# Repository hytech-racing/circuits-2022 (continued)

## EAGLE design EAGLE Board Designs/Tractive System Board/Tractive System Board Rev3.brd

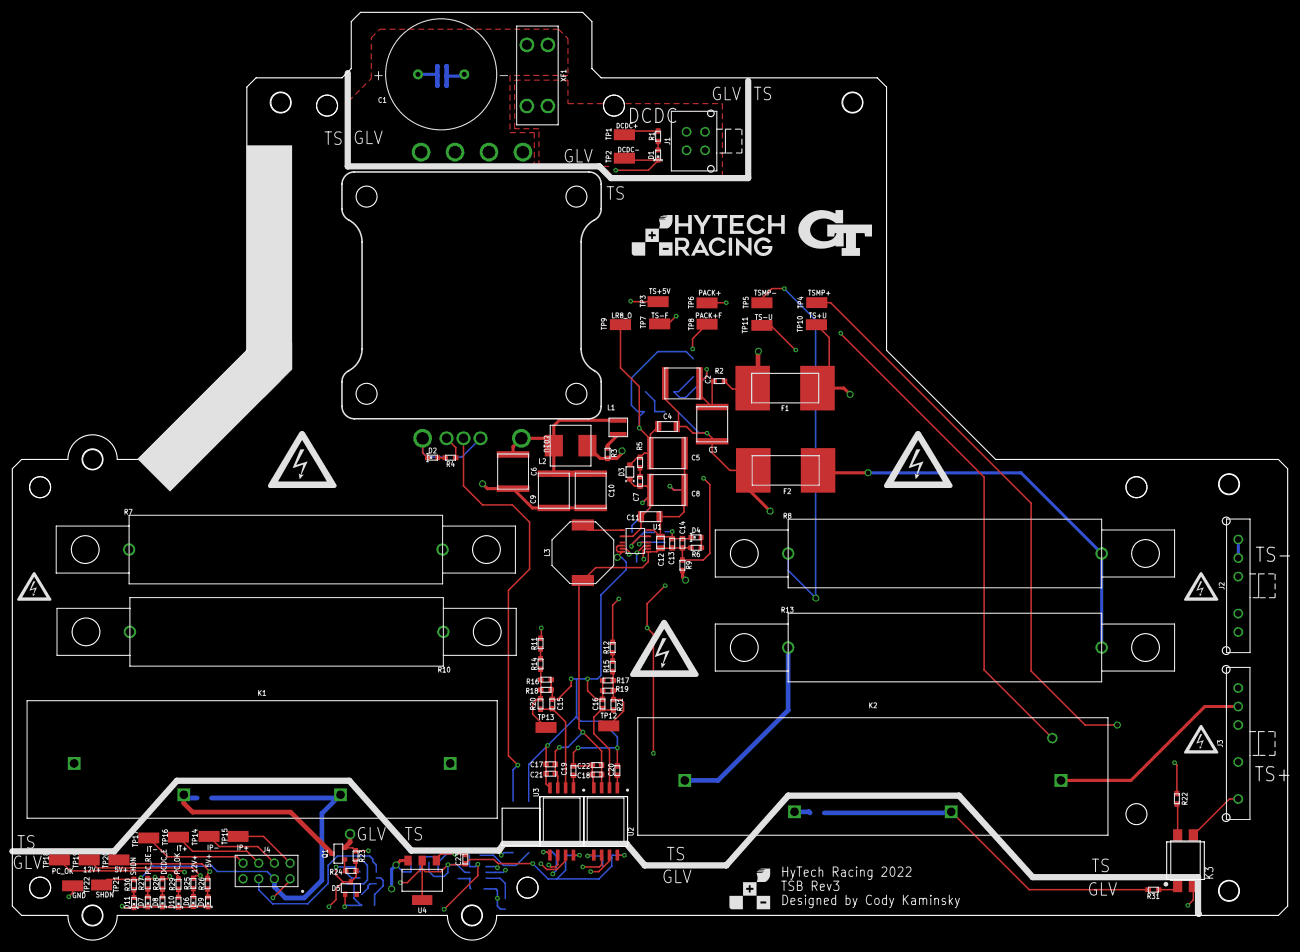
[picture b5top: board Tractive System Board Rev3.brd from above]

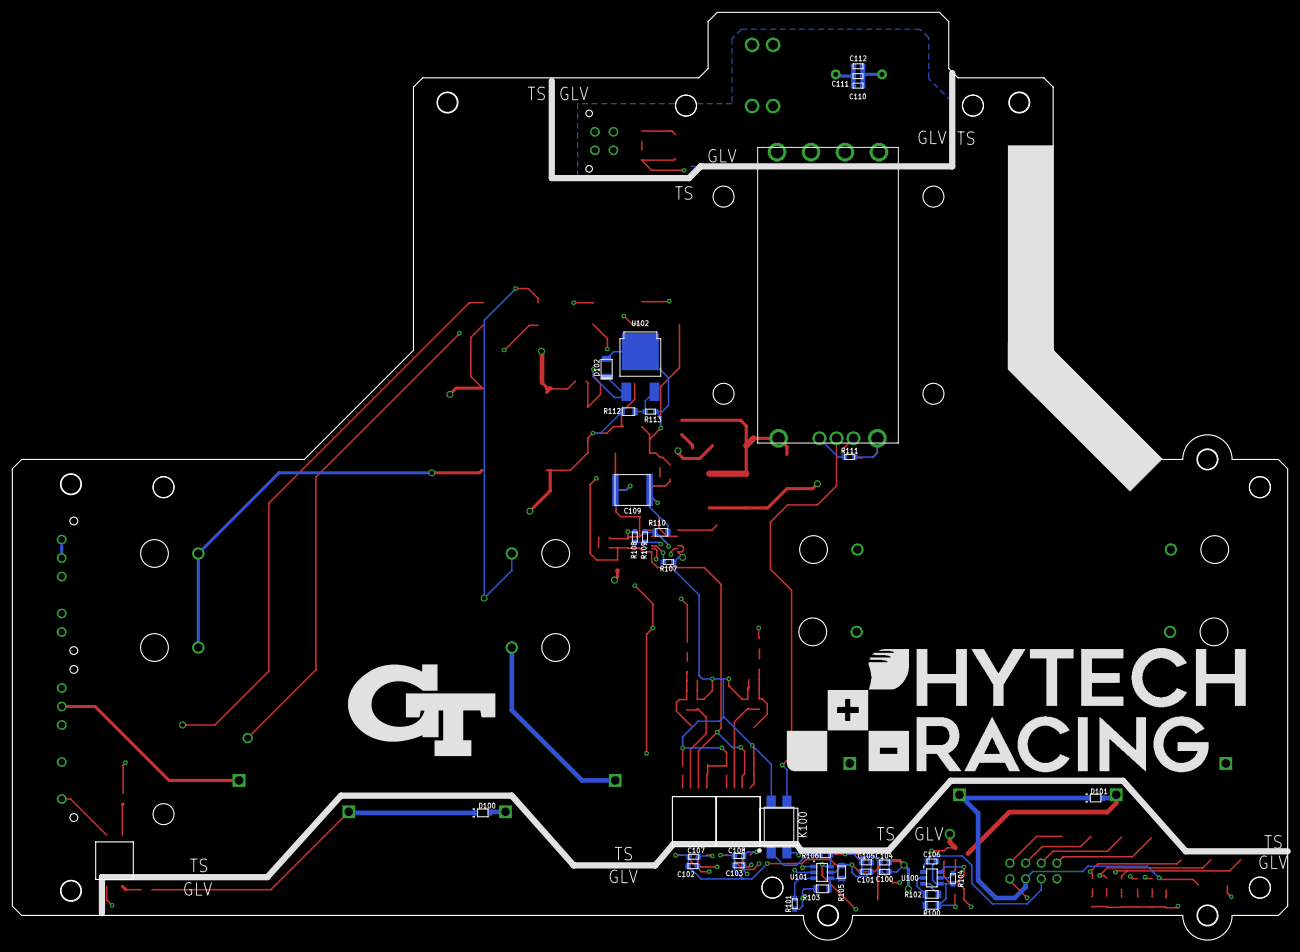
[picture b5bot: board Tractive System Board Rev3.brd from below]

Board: 4 copper layers, 206.7 x 150.3 mm, 183 parts (37 on the bottom side), 68 nets.

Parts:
$$$$$$U$5: HV_LARGE
$$$$$$U$6: HV_1.00"
$$$$$$U$7, $$$$$$U$8, $$$$$$U$9: MOUNTING_M3
$$$$$$U$10: HV_0.50"
$$$$U$1, $$$$U$2, $$$$U$3, $$$$U$4, $$$$U$6, $$$$U$9, $$$$U$10, $$$$U$13, $$$$U$18, $$$$U$19: MOUNTING_M3
$$$$U$5, $$$$U$8, $$$$U$15, $$$$U$17: GLV
$$$$U$7: LOGO_HYTECH_SQUARE_0.28"
$$$$U$11: HV_0.50"
$$$$U$12: HV_LARGE
$$$$U$14, $$$$U$16: TS
$$U$1: TS
$$U$2, $$U$3, $$U$5, $$U$6: MOUNTING_M3
$$U$4: GLV
$$U$7: LOGO_GT_0.50"
C1: CAPACITOR_POLAR__3600UF; EKYC*MM
C2, C10: CAPACITOR_2220_630V_0.1UF; 2220-CAP
C3, C6, C9: CAPACITOR_2220_630V_1UF; 2220-CAP
C4, C11: CAPACITOR_1206_250V_0.1UF; 1206-CAP
C5, C8, C109: CAPACITOR_2220_250V_1UF; 2220-CAP
C7, C15, C16: CAPACITOR_0603_10V_10NF; 0603-CAP
C12: CAPACITOR_0805_25V_22UF; 0805-CAP
C13, C104, C111: CAPACITOR_0603_25V_1UF; 0603-CAP
C14, C100: CAPACITOR_0603_25V_0.1UF; 0603-CAP
C17, C18, C19, C20, C21, C22, C103, C107: CAPACITOR_0603_10V_1UF; 0603-CAP
C23, C102, C105, C106, C108: CAPACITOR_0603_10V_0.1UF; 0603-CAP
C101: CAPACITOR_0603_10V_4.7UF; 0603-CAP
C110: CAPACITOR_0603_25V_10UF; 0603-CAP
C112: CAPACITOR_0603_35V_0.1UF; 0603-CAP
D1, D4, D6, D9: LED_0603_BLUE; 0603-LED
D2: LED_0603_RED; 0603-LED
D3, D100, D101: SCHOTTKY_SOD323_30V; SOD-323
D5: TVS_8V; SOT-23
D7: LED_0603_WHITE; 0603-LED
D8: LED_0603_YELLOW; 0603-LED
D10: LED_0603_GREEN; 0603-LED
D11: LED_0603_ORANGE; 0603-LED
D102: RECTIFIER_400V_SOD123; SOD123F
F1, F2: FUSE_0885_1.25; 0885
J1: CONNECTOR-4__; MOLEX_MICROFIT_PTH_VERTICAL_04_DUAL
J2: CONNECTOR-5_MICRO_V6S_; MOLEX_MICROFIT_PTH_VERTICAL_06_SINGLE_SPACED
J3: CONNECTOR-5_MICRO_V7S_; MOLEX_MICROFIT_PTH_VERTICAL_07_SINGLE_SPACED
J4: CONNECTOR-8_S_S; FLEX_STACK_PTH_08_DUAL
K1: RELAY_SPST_NO_3550_12; 335X
K2: RELAY_SPST_NC_POLARIZED_3550_12; 335X
K3: RELAY_SOLIDSTATE_NO_AG; DIP-4_AIRGAP
K100: RELAY_SOLIDSTATE_NC_AG; DIP-4_AIRGAP
L1: INDUCTOR_PA4334_3.6UH; PA4334
L2: INDUCTOR_WELMHI_56UH; WE-LMHI
L3: INDUCTOR_SRU1048_330UH; SRU1048
Q1: TRANSISTOR_N_MOS__PMV15ENEA; SOT-23
R1, R4, R6, R25, R26, R27, R28, R29, R30, R31, R106: RESISTOR_0603_1K; 0603-RES
R2, R22: RESISTOR_0603_39; 0603-RES
R3: RESISTOR_0603_1.62; 0603-RES
R5, R23: RESISTOR_0603_10K; 0603-RES
R7, R8, R13: RESISTOR_B20_10K; B20
R9: RESISTOR_0603_180; 0603-RES
R10: RESISTOR_B20_750; B20
R11, R12: RESISTOR_0603_HV750K; 0603-RES
R14, R15: RESISTOR_0603_360K; 0603-RES
R16, R17, R18, R19: RESISTOR_0603_HV75K; 0603-RES
R20, R21: RESISTOR_0603_33.2K; 0603-RES
R24: RESISTOR_0603_10; 0603-RES
R100, R103: RESISTOR_0805_1M; 0805-RES
R101, R104, R107: RESISTOR_0603_75K; 0603-RES
R102, R105: RESISTOR_0805_523K; 0805-RES
R108: RESISTOR_0603_8.35K; 0603-RES
R109: RESISTOR_0603_13.3K; 0603-RES
R110: RESISTOR_0805_976K; 0805-RES
R111: RESISTOR_0603_DNP; 0603-RES
R112: RESISTOR_0805_HV365K; 0805-RES
R113: RESISTOR_0603_3.32K; 0603-RES
TP1, TP2, TP3, TP4, TP5, TP6, TP7, TP8, TP9, TP10, TP11, TP12, TP13, TP14, TP15, TP16, TP17, TP18, TP19, TP20, TP21, TP22: TEST_POINT; MICRO_MINIATURE
U1: LTC3639; MSE16(12)
U2, U3: ISO224B_AIRGAP; SOIC-08(WIDE,0.295")-AIRGAP
U4: VOLTAGE_REGULATOR_SOT223_5V; SOT223
U100, U101: LTC6994-2; SOT-23-6
U102: VOLTAGE_REGULATOR_ADJ_LR8_DPAK; DPAK(2-7K1S)
U103: DCM4623TD2J13D0T70; DCM4623
U$1, U$6: GLV
U$5, U$7, U$11, U$12: TS
U$8: LOGO_HYTECH_MEDIUM
U$9: MOUNTING_M3
U$10: HV_0.50"
U$100: LOGO_HYTECH_EXTRA_LARGE
U$101: LOGO_GT_LARGE
XF1: FUSE_HOLDER_MINIBLADEPTH; 3568

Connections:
+5V: C23.1, C101.1, C102.1, C103.1, C105.1, C107.1, C108.1, R26.1, R105.2, TP20.1, U2.8, U3.8, U4.2, U4.4, U101.5
+12V: C100.1, C104.1, J4.1, R25.2, TP19.1, U4.3
DCDC+: J1.1, J1.3, R1.2, TP1.1, XF1.3, XF1.4
DCDC-: C1.-, C110.1, C111.1, C112.1, D1.1, J1.2, J1.4, TP2.1, U103.7, U103.9
DCDC_ENABLE: D5.3, R23.2, R24.1, R28.2, U100.4, U101.1
ENABLE: K100.4, U103.3
GND: C23.2, C100.2, C101.2, C102.2, C103.2, C104.2, C105.2, C106.2, C107.2, C108.2, D5.1, D6.1, D7.1, D8.1, D9.1, D10.1, D11.1, D100.A, J4.4, K2.3, K3.2, K100.2, Q1.2, R23.1, R100.1, R101.1, R103.1, R104.1, TP22.1, U2.5, U3.5, U4.1, U100.6, U101.2
IP+: J4.5, TP15.1, U3.7
IP-: J4.6, TP14.1, U3.6
IT+: J4.7, TP16.1, U2.7
IT-: J4.8, TP17.1, U2.6
LED+: J2.3, R9.2
LR8_O: C4.1, C5.1, D3.A, D102.A, R5.1, R113.2, TP9.1, U102.2
unnamed: R11.1, R14.2
unnamed: R108.2, R109.1, U1.12
unnamed: Q1.1, R24.2
unnamed: R103.2, R105.1, U101.6
unnamed: R109.2, R110.1, U1.14
unnamed: K100.1, R106.2
unnamed: R12.1, R15.2
unnamed: R112.2, R113.1, U102.3
unnamed: R100.2, R102.1, U100.2
unnamed: R102.2, U100.3
unnamed: R104.2, U100.5
unnamed: R101.2, U101.3
unnamed: C2.1, C3.1, D102.C, R2.2, U102.1
unnamed: R27.2, R106.1, U101.4
unnamed: D7.2, R27.1
unnamed: D1.2, R1.1
unnamed: D10.2, R29.1
unnamed: D8.2, R28.1
unnamed: D6.2, R25.1
unnamed: L1.2, R3.1
unnamed: D9.2, R26.2
unnamed: D11.2, R30.1
unnamed: D4.2, R6.1
unnamed: C6.1, C9.1, C10.1, L1.1, L2.1, U103.1
unnamed: D101.A, K1.3, Q1.3
unnamed: D2.2, R4.2
unnamed: R4.1, U103.4
unnamed: R111.1, U103.2
unnamed: C1.+, C110.2, C111.2, C112.2, U103.6, U103.8, XF1.1, XF1.2
unnamed: K1.4, R10.1
unnamed: K2.4, R13.2
unnamed: K3.1, R31.1
unnamed: K3.3, R22.2
unnamed: C7.2, R5.2
unnamed: C7.1, C8.1, C11.1, C109.1, D3.C, R110.2, U1.3
unnamed: C15.1, R20.2, U3.2
unnamed: C16.1, R21.2, U2.2
unnamed: R107.2, U1.11
unnamed: L3.1, U1.1
unnamed: C19.1, U3.1
unnamed: C20.1, U2.1
unnamed: U1.7, U1.10
PACK+: J3.5, K1.1, K3.4, TP6.1
PACK+FUSED: R11.2, R22.1, TP8.1
PRECHARGE_OK: C106.1, J4.3, R29.2, TP18.1, U100.1
P_DO: R14.1, R16.2, R18.2, R20.1, TP13.1
SHDN: D100.C, D101.C, J4.2, K1.2, K2.2, R30.2, R31.2, TP21.1
TS+5V: C12.1, C13.1, C14.1, C17.1, C18.1, C21.1, C22.1, L3.2, R6.2, R9.1, TP3.1, U1.9, U2.3, U3.3
TS+FUSED: F1.2, J3.4, L2.2, R2.1, R3.2, R12.2
TS+UNFUSED: F1.1, J3.1, J3.2, K2.1, R7.1, R10.2, TP10.1
TS-FUSED: C2.2, C3.2, C4.2, C5.2, C6.2, C8.2, C9.2, C10.2, C11.2, C12.2, C13.2, C14.2, C15.2, C16.2, C17.2, C18.2, C19.2, C20.2, C21.2, C22.2, C109.2, D2.1, D4.1, F2.2, J2.1, J2.2, K100.3, R16.1, R17.1, R18.1, R19.1, R107.1, R108.1, R111.2, R112.1, TP7.1, U1.6, U1.8, U1.16, U2.4, U3.4, U103.5
TS-UNFUSED: F2.1, J2.5, R8.1, R13.1, TP11.1
TSMP+: J3.3, R7.2, TP4.1
TSMP-: J2.4, R8.2, TP5.1
TS_DO: R15.1, R17.2, R19.2, R21.1, TP12.1

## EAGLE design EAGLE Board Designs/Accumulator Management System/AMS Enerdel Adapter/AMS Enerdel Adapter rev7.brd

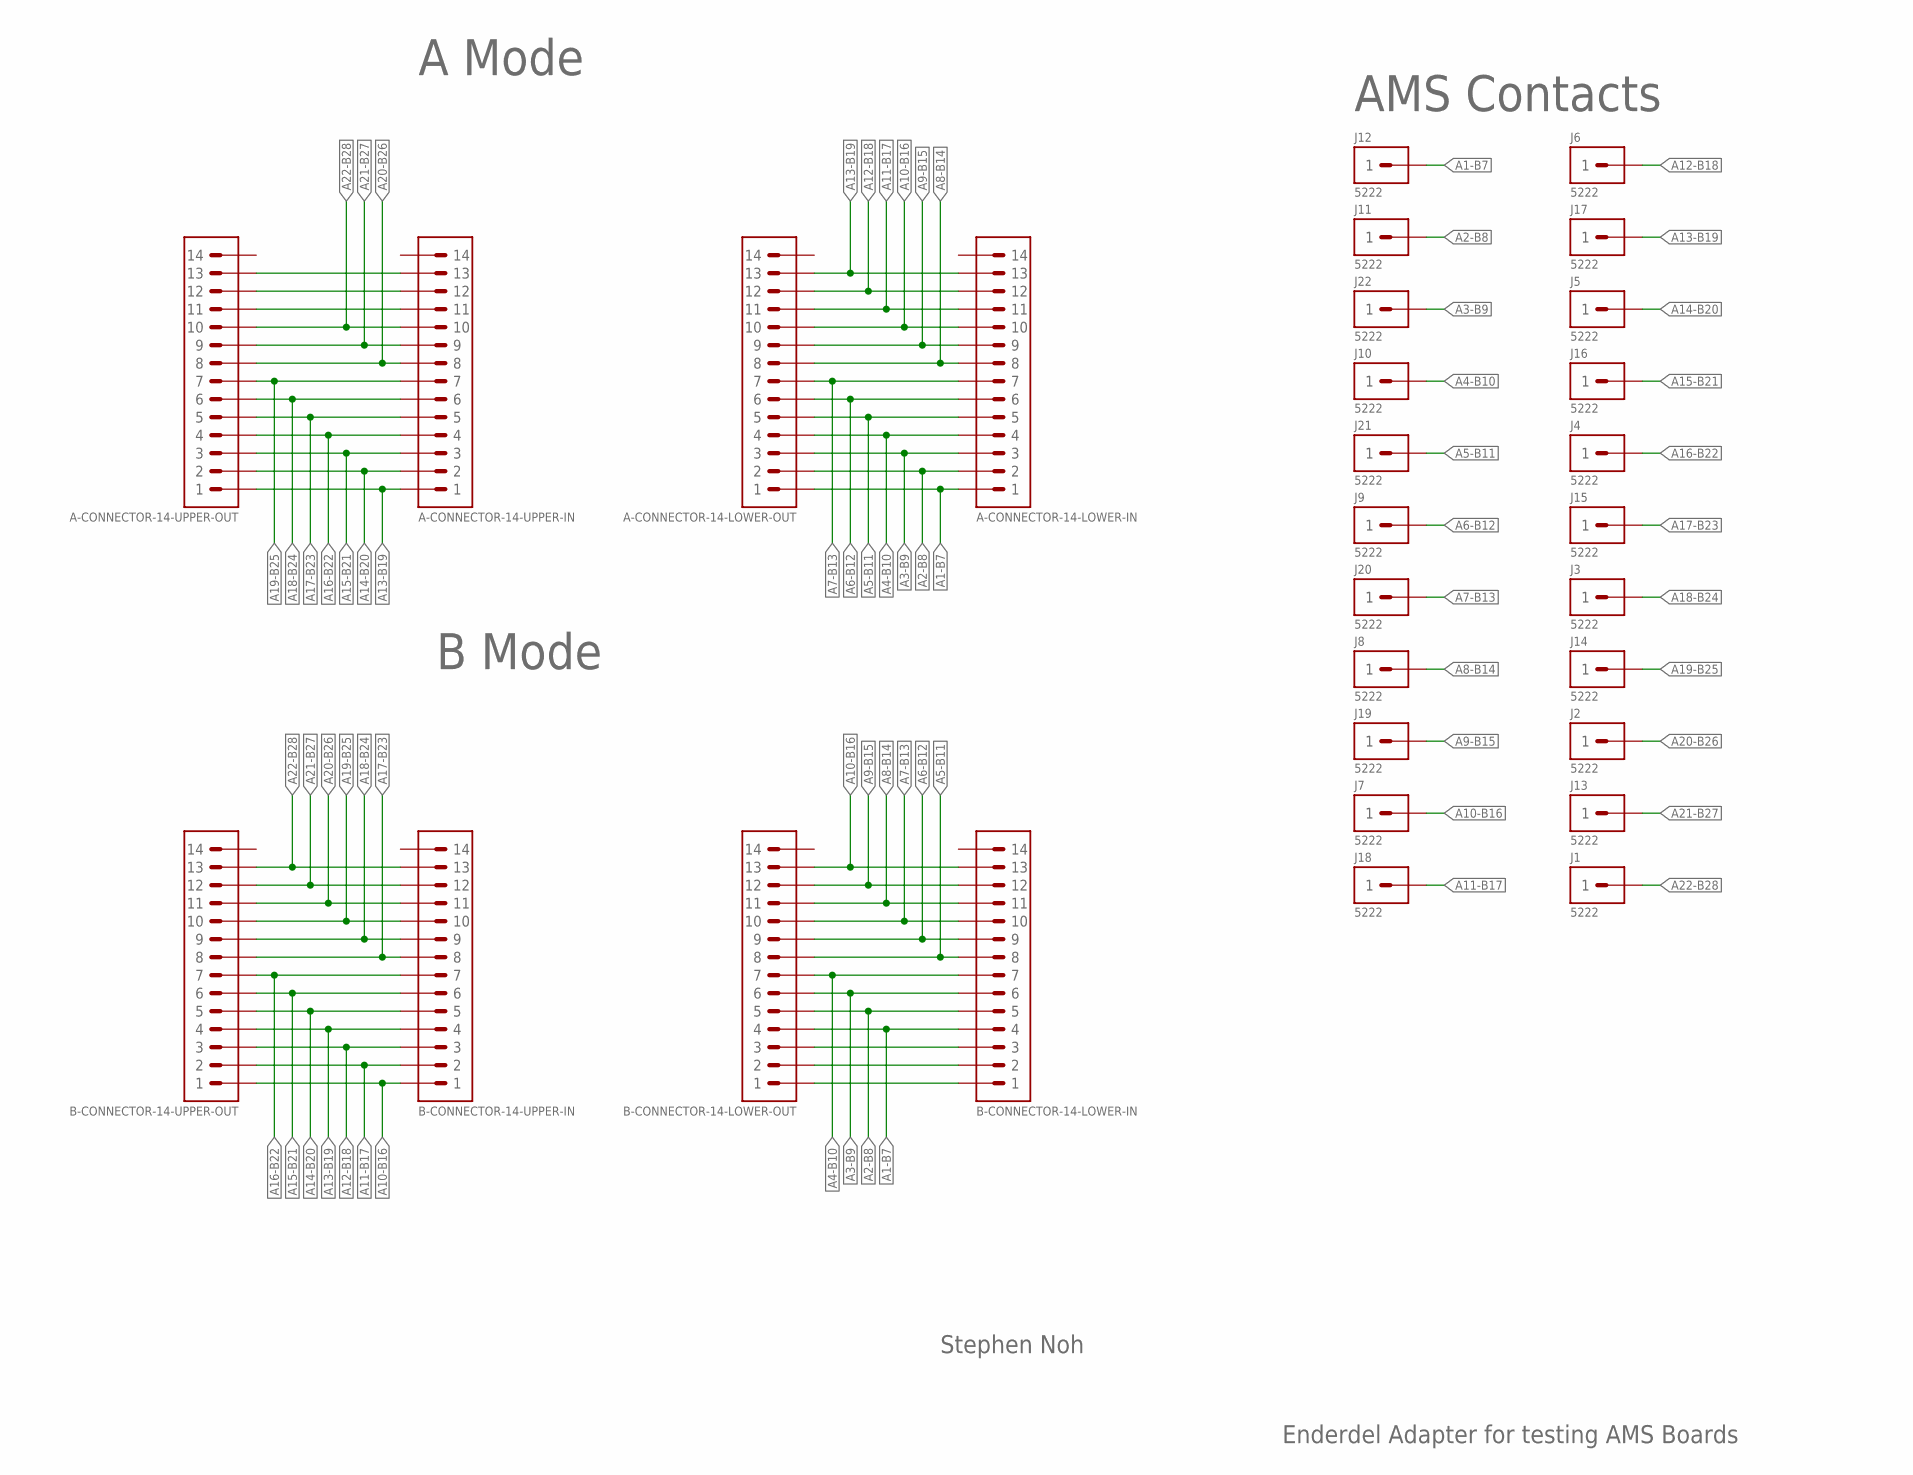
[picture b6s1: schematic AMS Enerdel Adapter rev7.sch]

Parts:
A-CONNECTOR-14-LOWER-IN, A-CONNECTOR-14-LOWER-OUT: CONNECTOR-14_MINIFIT_; MOLEX_MINIFIT_PTH_14
A-CONNECTOR-14-UPPER-IN, A-CONNECTOR-14-UPPER-OUT: CONNECTOR-14_NANOFIT_; MOLEX_NANOFIT_PTH_14
B-CONNECTOR-14-LOWER-IN, B-CONNECTOR-14-LOWER-OUT: CONNECTOR-14_MINIFIT_; MOLEX_MINIFIT_PTH_14
B-CONNECTOR-14-UPPER-IN, B-CONNECTOR-14-UPPER-OUT: CONNECTOR-14_NANOFIT_; MOLEX_NANOFIT_PTH_14
J1, J2, J3, J4, J5, J6, J7, J8, J9, J10, J11, J12, J13, J14, J15, J16, J17, J18, J19, J20, J21, J22: CONNECTOR-1_5222_; 5222

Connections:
A1-B7: A-CONNECTOR-14-LOWER-IN.1, A-CONNECTOR-14-LOWER-OUT.1, B-CONNECTOR-14-LOWER-IN.4, B-CONNECTOR-14-LOWER-OUT.4, J12.1
A2-B8: A-CONNECTOR-14-LOWER-IN.2, A-CONNECTOR-14-LOWER-OUT.2, B-CONNECTOR-14-LOWER-IN.5, B-CONNECTOR-14-LOWER-OUT.5, J11.1
A3-B9: A-CONNECTOR-14-LOWER-IN.3, A-CONNECTOR-14-LOWER-OUT.3, B-CONNECTOR-14-LOWER-IN.6, B-CONNECTOR-14-LOWER-OUT.6, J22.1
A4-B10: A-CONNECTOR-14-LOWER-IN.4, A-CONNECTOR-14-LOWER-OUT.4, B-CONNECTOR-14-LOWER-IN.7, B-CONNECTOR-14-LOWER-OUT.7, J10.1
A5-B11: A-CONNECTOR-14-LOWER-IN.5, A-CONNECTOR-14-LOWER-OUT.5, B-CONNECTOR-14-LOWER-IN.8, B-CONNECTOR-14-LOWER-OUT.8, J21.1
A6-B12: A-CONNECTOR-14-LOWER-IN.6, A-CONNECTOR-14-LOWER-OUT.6, B-CONNECTOR-14-LOWER-IN.9, B-CONNECTOR-14-LOWER-OUT.9, J9.1
A7-B13: A-CONNECTOR-14-LOWER-IN.7, A-CONNECTOR-14-LOWER-OUT.7, B-CONNECTOR-14-LOWER-IN.10, B-CONNECTOR-14-LOWER-OUT.10, J20.1
A8-B14: A-CONNECTOR-14-LOWER-IN.8, A-CONNECTOR-14-LOWER-OUT.8, B-CONNECTOR-14-LOWER-IN.11, B-CONNECTOR-14-LOWER-OUT.11, J8.1
A9-B15: A-CONNECTOR-14-LOWER-IN.9, A-CONNECTOR-14-LOWER-OUT.9, B-CONNECTOR-14-LOWER-IN.12, B-CONNECTOR-14-LOWER-OUT.12, J19.1
A10-B16: A-CONNECTOR-14-LOWER-IN.10, A-CONNECTOR-14-LOWER-OUT.10, B-CONNECTOR-14-LOWER-IN.13, B-CONNECTOR-14-LOWER-OUT.13, B-CONNECTOR-14-UPPER-IN.1, B-CONNECTOR-14-UPPER-OUT.1, J7.1
A11-B17: A-CONNECTOR-14-LOWER-IN.11, A-CONNECTOR-14-LOWER-OUT.11, B-CONNECTOR-14-UPPER-IN.2, B-CONNECTOR-14-UPPER-OUT.2, J18.1
A12-B18: A-CONNECTOR-14-LOWER-IN.12, A-CONNECTOR-14-LOWER-OUT.12, B-CONNECTOR-14-UPPER-IN.3, B-CONNECTOR-14-UPPER-OUT.3, J6.1
A13-B19: A-CONNECTOR-14-LOWER-IN.13, A-CONNECTOR-14-LOWER-OUT.13, A-CONNECTOR-14-UPPER-IN.1, A-CONNECTOR-14-UPPER-OUT.1, B-CONNECTOR-14-UPPER-IN.4, B-CONNECTOR-14-UPPER-OUT.4, J17.1
A14-B20: A-CONNECTOR-14-UPPER-IN.2, A-CONNECTOR-14-UPPER-OUT.2, B-CONNECTOR-14-UPPER-IN.5, B-CONNECTOR-14-UPPER-OUT.5, J5.1
A15-B21: A-CONNECTOR-14-UPPER-IN.3, A-CONNECTOR-14-UPPER-OUT.3, B-CONNECTOR-14-UPPER-IN.6, B-CONNECTOR-14-UPPER-OUT.6, J16.1
A16-B22: A-CONNECTOR-14-UPPER-IN.4, A-CONNECTOR-14-UPPER-OUT.4, B-CONNECTOR-14-UPPER-IN.7, B-CONNECTOR-14-UPPER-OUT.7, J4.1
A17-B23: A-CONNECTOR-14-UPPER-IN.5, A-CONNECTOR-14-UPPER-OUT.5, B-CONNECTOR-14-UPPER-IN.8, B-CONNECTOR-14-UPPER-OUT.8, J15.1
A18-B24: A-CONNECTOR-14-UPPER-IN.6, A-CONNECTOR-14-UPPER-OUT.6, B-CONNECTOR-14-UPPER-IN.9, B-CONNECTOR-14-UPPER-OUT.9, J3.1
A19-B25: A-CONNECTOR-14-UPPER-IN.7, A-CONNECTOR-14-UPPER-OUT.7, B-CONNECTOR-14-UPPER-IN.10, B-CONNECTOR-14-UPPER-OUT.10, J14.1
A20-B26: A-CONNECTOR-14-UPPER-IN.8, A-CONNECTOR-14-UPPER-OUT.8, B-CONNECTOR-14-UPPER-IN.11, B-CONNECTOR-14-UPPER-OUT.11, J2.1
A21-B27: A-CONNECTOR-14-UPPER-IN.9, A-CONNECTOR-14-UPPER-OUT.9, B-CONNECTOR-14-UPPER-IN.12, B-CONNECTOR-14-UPPER-OUT.12, J13.1
A22-B28: A-CONNECTOR-14-UPPER-IN.10, A-CONNECTOR-14-UPPER-OUT.10, B-CONNECTOR-14-UPPER-IN.13, B-CONNECTOR-14-UPPER-OUT.13, J1.1
B-PASS1: B-CONNECTOR-14-LOWER-IN.3, B-CONNECTOR-14-LOWER-OUT.3
B-PASS2: B-CONNECTOR-14-LOWER-IN.2, B-CONNECTOR-14-LOWER-OUT.2
B-PASS3: B-CONNECTOR-14-LOWER-IN.1, B-CONNECTOR-14-LOWER-OUT.1
unnamed: A-CONNECTOR-14-UPPER-IN.11, A-CONNECTOR-14-UPPER-OUT.11
unnamed: A-CONNECTOR-14-UPPER-IN.12, A-CONNECTOR-14-UPPER-OUT.12
unnamed: A-CONNECTOR-14-UPPER-IN.13, A-CONNECTOR-14-UPPER-OUT.13

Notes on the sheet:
Stephen Noh
AMS Contacts
A Mode
Enderdel Adapter for testing AMS Boards
B Mode

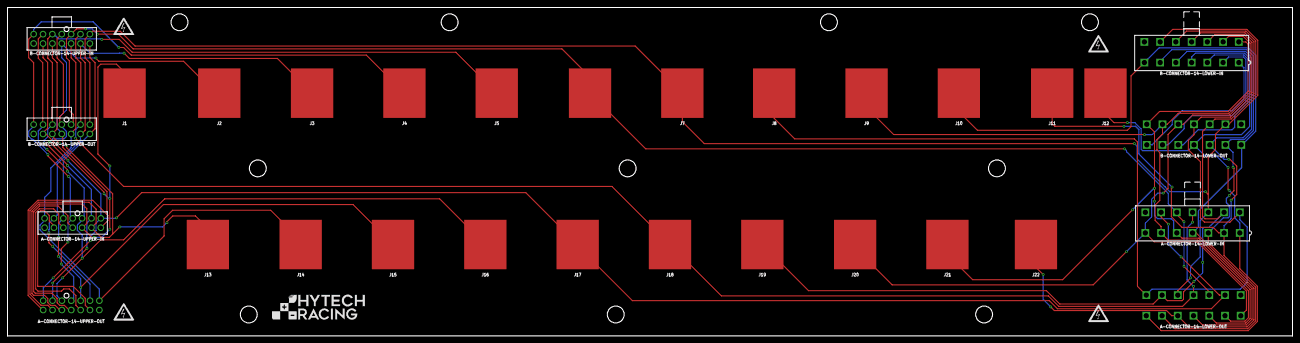
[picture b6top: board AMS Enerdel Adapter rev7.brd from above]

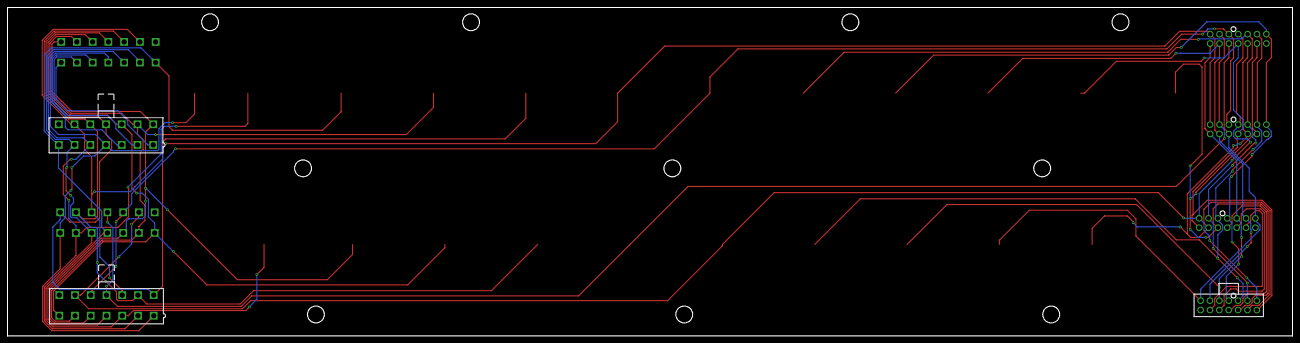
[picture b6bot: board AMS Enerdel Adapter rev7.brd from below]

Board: 2 copper layers, 342.9 x 87.6 mm, 35 parts (3 on the bottom side), 28 nets.

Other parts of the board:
U$1, U$2, U$3, U$4: HV_0.50"
U$5: LOGO_HYTECH_1.0"

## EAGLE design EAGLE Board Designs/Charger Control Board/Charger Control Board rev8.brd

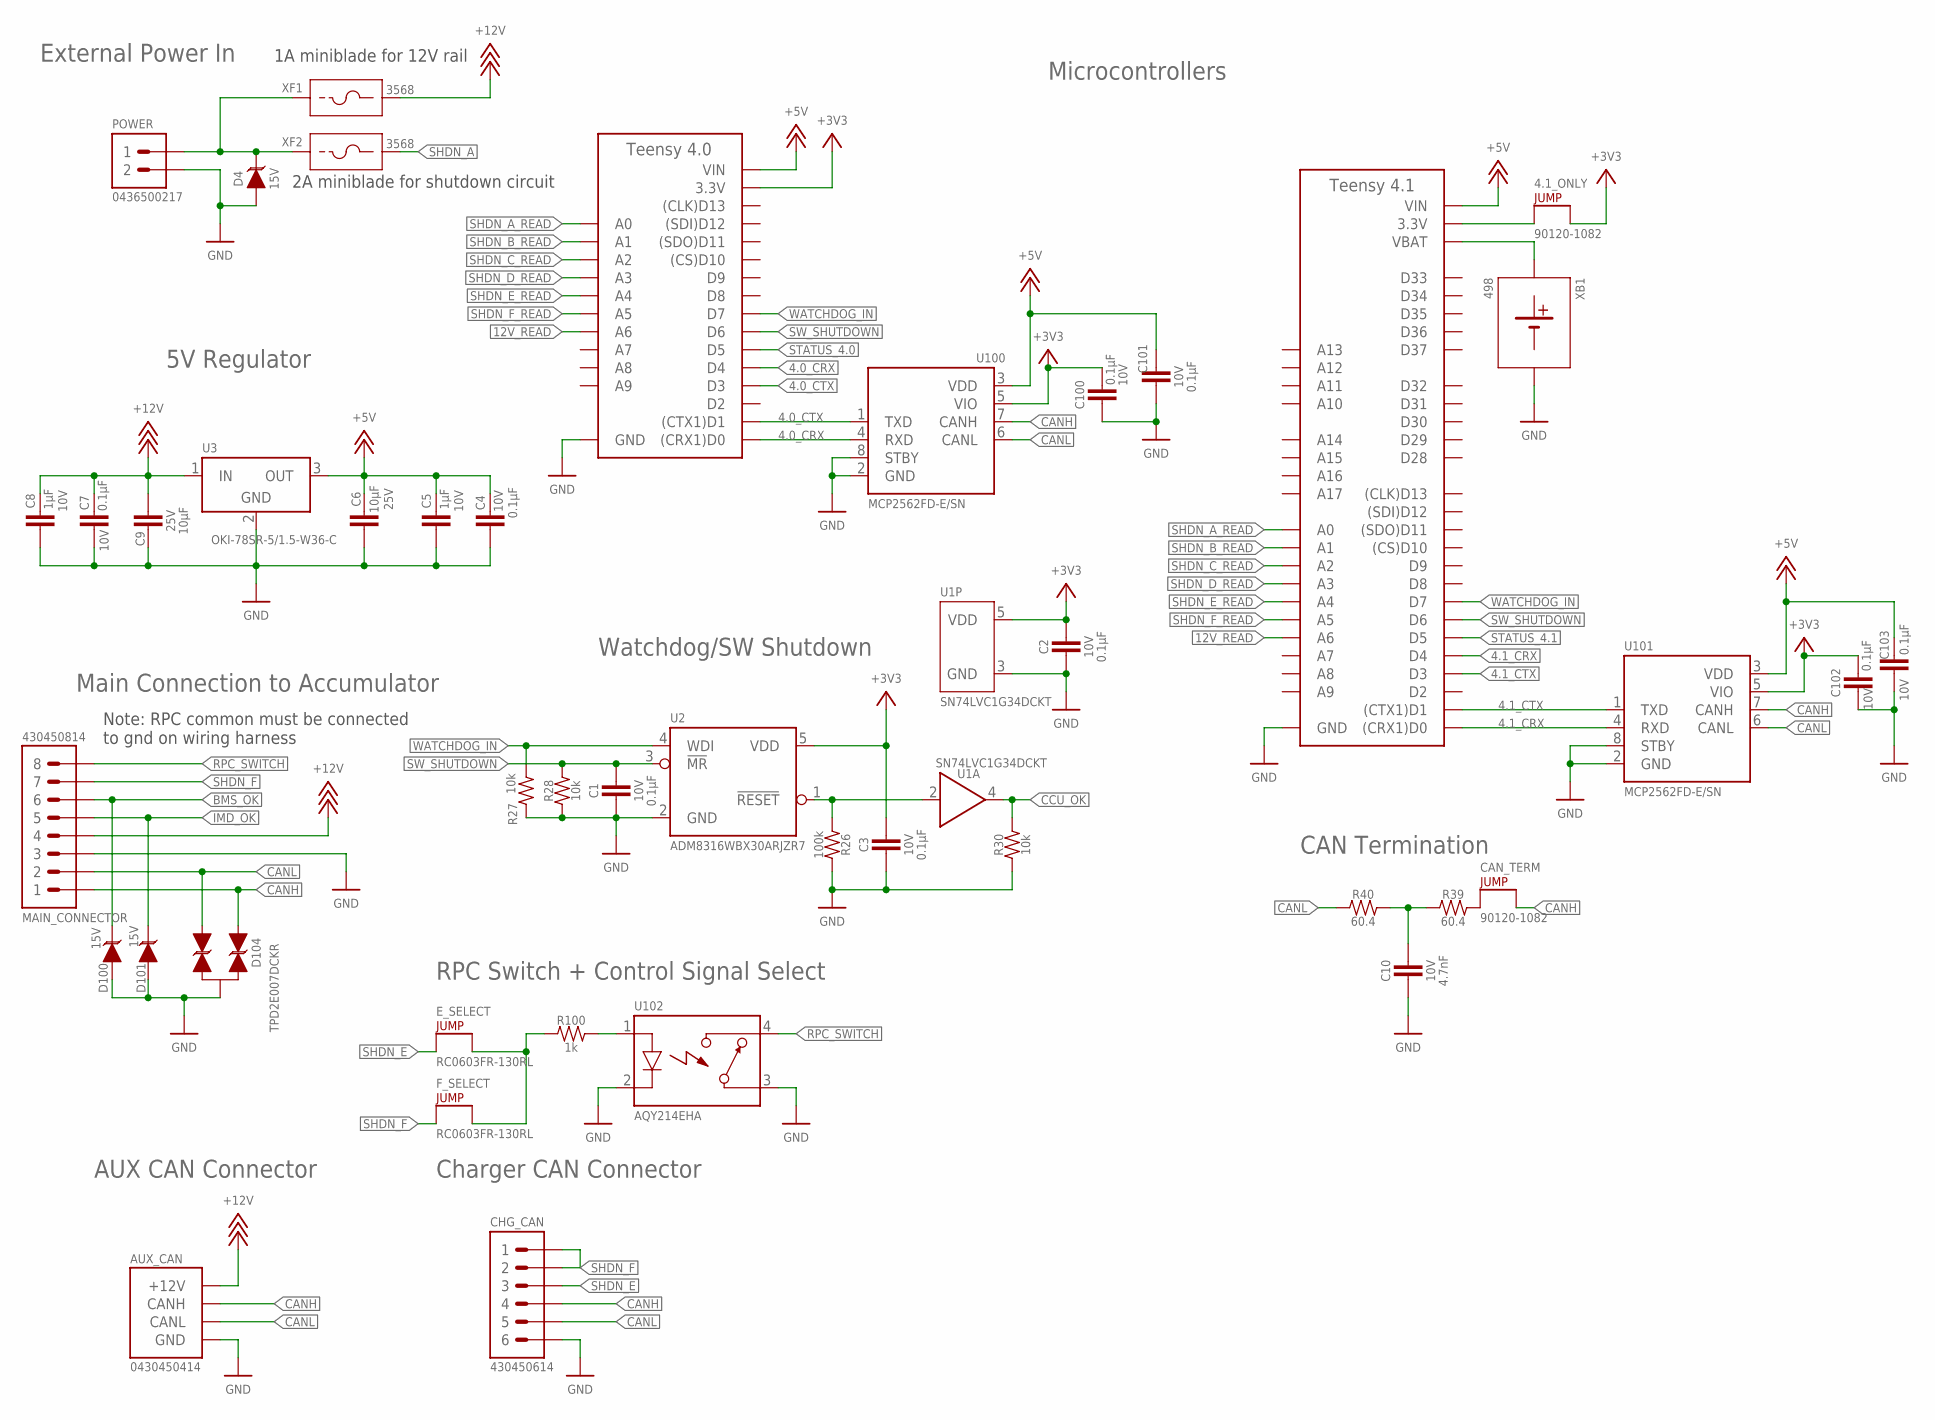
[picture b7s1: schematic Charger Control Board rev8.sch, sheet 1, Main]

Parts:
4.1_ONLY: JUMPER__1X02; 1X02
A1: TEENSY_4.1; TEENSY_LONG_EXT
A2: TEENSY_4.0; TEENSY_SHORT
AUX_CAN: CONNECTOR-CAN_MF_T_V_BLACK; MOLEX_MICROFIT_PTH_VERTICAL_04_DUAL
C1, C2, C3, C4, C7, C100, C101, C102, C103: CAPACITOR_0603_10V_0.1UF; 0603-CAP
C5, C8: CAPACITOR_0603_10V_1UF; 0603-CAP
C6, C9: CAPACITOR_0603_25V_10UF; 0603-CAP
C10: CAPACITOR_0603_10V_4.7NF; 0603-CAP
CAN_TERM: JUMPER__1X02; 1X02
CHG_CAN: CONNECTOR-6_MF_T_V_BLACK; MOLEX_MICROFIT_PTH_VERTICAL_06_DUAL
D4, D100, D101: TVS_15V; SOT-23
D104: TVS_BIDIRECTIONAL_DUAL; SC-70-3
E_SELECT: JUMPER_0603_; 0603-RES
F_SELECT: JUMPER_0603_; 0603-RES
MAIN_CONNECTOR: CONNECTOR-8_MF_T_V_BLACK; MOLEX_MICROFIT_PTH_VERTICAL_08_DUAL
POWER: CONNECTOR-2_MF_T_V_; MOLEX_MICROFIT_PTH_VERTICAL_02_SINGLE
R26: RESISTOR_0603_100K; 0603-RES
R27, R28, R30: RESISTOR_0603_10K; 0603-RES
R39, R40: RESISTOR_0603_60.4; 0603-RES
R100: RESISTOR_0603_1K; 0603-RES
U1: LOGICGATE_BUFFER; SC-70-5
U2: ADM8316WBX30; SOT-23-5
U3: VOLTAGE_REGULATOR_MODULE_OKI-78SR_5V; OKI-78SR
U100, U101: MCP2562FD; SOIC-08(NARROW,0.15")
U102: RELAY_SOLIDSTATE_NO; DIP-4
XB1: BATTERY_HOLDER_KEYSTONE_498; 498
XF1, XF2: FUSE_HOLDER_MINIBLADEPTH; 3568

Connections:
4.0_CRX: A2.D0 ((CRX1)D0), A2.D4, U100.4 (RXD)
4.0_CTX: A2.D1 ((CTX1)D1), A2.D3, U100.1 (TXD)
4.1_CRX: A1.D0 ((CRX1)D0), A1.D4, U101.4 (RXD)
4.1_CTX: A1.D1 ((CTX1)D1), A1.D3, U101.1 (TXD)
12V_READ: A1.D20 (A6), A2.D20 (A6); also elsewhere on the board
+3V3: 4.1_ONLY.2, A2.3.3V, C2.2, C3.2, C100.2, C102.2, U1.5 (VDD), U2.5 (VDD), U100.5 (VIO), U101.5 (VIO); also elsewhere on the board
+5V: A1.VIN, A2.VIN, C4.2, C5.1, C6.1, C101.2, C103.2, U3.3 (OUT), U100.3 (VDD), U101.3 (VDD); also elsewhere on the board
+12V: AUX_CAN.1 (+12V), C7.2, C8.1, C9.1, MAIN_CONNECTOR.4, U3.1 (IN), XF1.3 (2), XF1.4 (2); also elsewhere on the board
BMS_OK: D100.3 (C), MAIN_CONNECTOR.6; also elsewhere on the board
CANH: AUX_CAN.4 (CANH), CAN_TERM.2, CHG_CAN.4, D104.1 (C1), MAIN_CONNECTOR.1, U100.7 (CANH), U101.7 (CANH)
CANL: AUX_CAN.3 (CANL), CHG_CAN.5, D104.2 (C2), MAIN_CONNECTOR.2, R40.1, U100.6 (CANL), U101.6 (CANL)
CCU_OK: R30.2, U1.4 (OUT); also elsewhere on the board
GND: A1.AGND/GND (GND), A1.GND, A1.GND@2 (GND), A2.AGND/GND (GND), A2.GND, AUX_CAN.2 (GND), C1.1, C2.1, C3.1, C4.1, C5.2, C6.2, C7.1, C8.2, C9.2, C10.2, C100.1, C101.1, C102.1, C103.1, CHG_CAN.6, D4.1 (A), D100.1 (A), D101.1 (A), D104.3 (A), MAIN_CONNECTOR.3, POWER.2, R26.2, R27.2, R28.1, R30.1, U1.3 (GND), U2.2 (GND), U3.2 (GND), U100.2 (GND), U100.8 (STBY), U101.2 (GND), U101.8 (STBY), U102.2 (CONTROL-), U102.3 (CONTACT1), XB1.2 (MINUS); also elsewhere on the board
IMD_OK: D101.3 (C), MAIN_CONNECTOR.5; also elsewhere on the board
unnamed: D4.3 (C), POWER.1, XF1.1, XF1.2 (1), XF2.1, XF2.2 (1)
unnamed: R26.1, U1.2 (IN), U2.1 (!RESET!)
unnamed: CAN_TERM.1, R39.2
unnamed: E_SELECT.2, F_SELECT.2, R100.1
unnamed: A1.VBAT, XB1.1 (PLUS)
unnamed: C10.1, R39.1, R40.2
unnamed: R100.2, U102.1 (CONTROL+)
unnamed: 4.1_ONLY.1, A1.3V3 (3.3V), A1.3V3@2 (3.3V), A1.3V3@3 (3.3V)
RPC_SWITCH: MAIN_CONNECTOR.8, U102.4 (CONTACT2)
SHDN_A: XF2.3 (2), XF2.4 (2); also elsewhere on the board
SHDN_A_READ: A1.D14 (A0), A2.D14 (A0); also elsewhere on the board
SHDN_B_READ: A1.D15 (A1), A2.D15 (A1); also elsewhere on the board
SHDN_C_READ: A1.D16 (A2), A2.D16 (A2); also elsewhere on the board
SHDN_D_READ: A1.D17 (A3), A2.D17 (A3); also elsewhere on the board
SHDN_E: CHG_CAN.3, E_SELECT.1; also elsewhere on the board
SHDN_E_READ: A1.D18 (A4), A2.D18 (A4); also elsewhere on the board
SHDN_F: CHG_CAN.1, CHG_CAN.2, F_SELECT.1, MAIN_CONNECTOR.7; also elsewhere on the board
SHDN_F_READ: A1.D19 (A5), A2.D19 (A5); also elsewhere on the board
STATUS_4.0: A2.D5; also elsewhere on the board
STATUS_4.1: A1.D5; also elsewhere on the board
SW_SHUTDOWN: A1.D6, A2.D6, C1.2, R28.2, U2.3 (!MR!)
WATCHDOG_IN: A1.D7, A2.D7, R27.1, U2.4 (WDI)

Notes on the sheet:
External Power In
5V Regulator
Main Connection to Accumulator
CAN Termination
Microcontrollers
Watchdog/SW Shutdown
Charger CAN Connector
AUX CAN Connector
1A miniblade for 12V rail
2A miniblade for shutdown circuit
RPC Switch + Control Signal Select
Note: RPC common must be connected to gnd on wiring harness

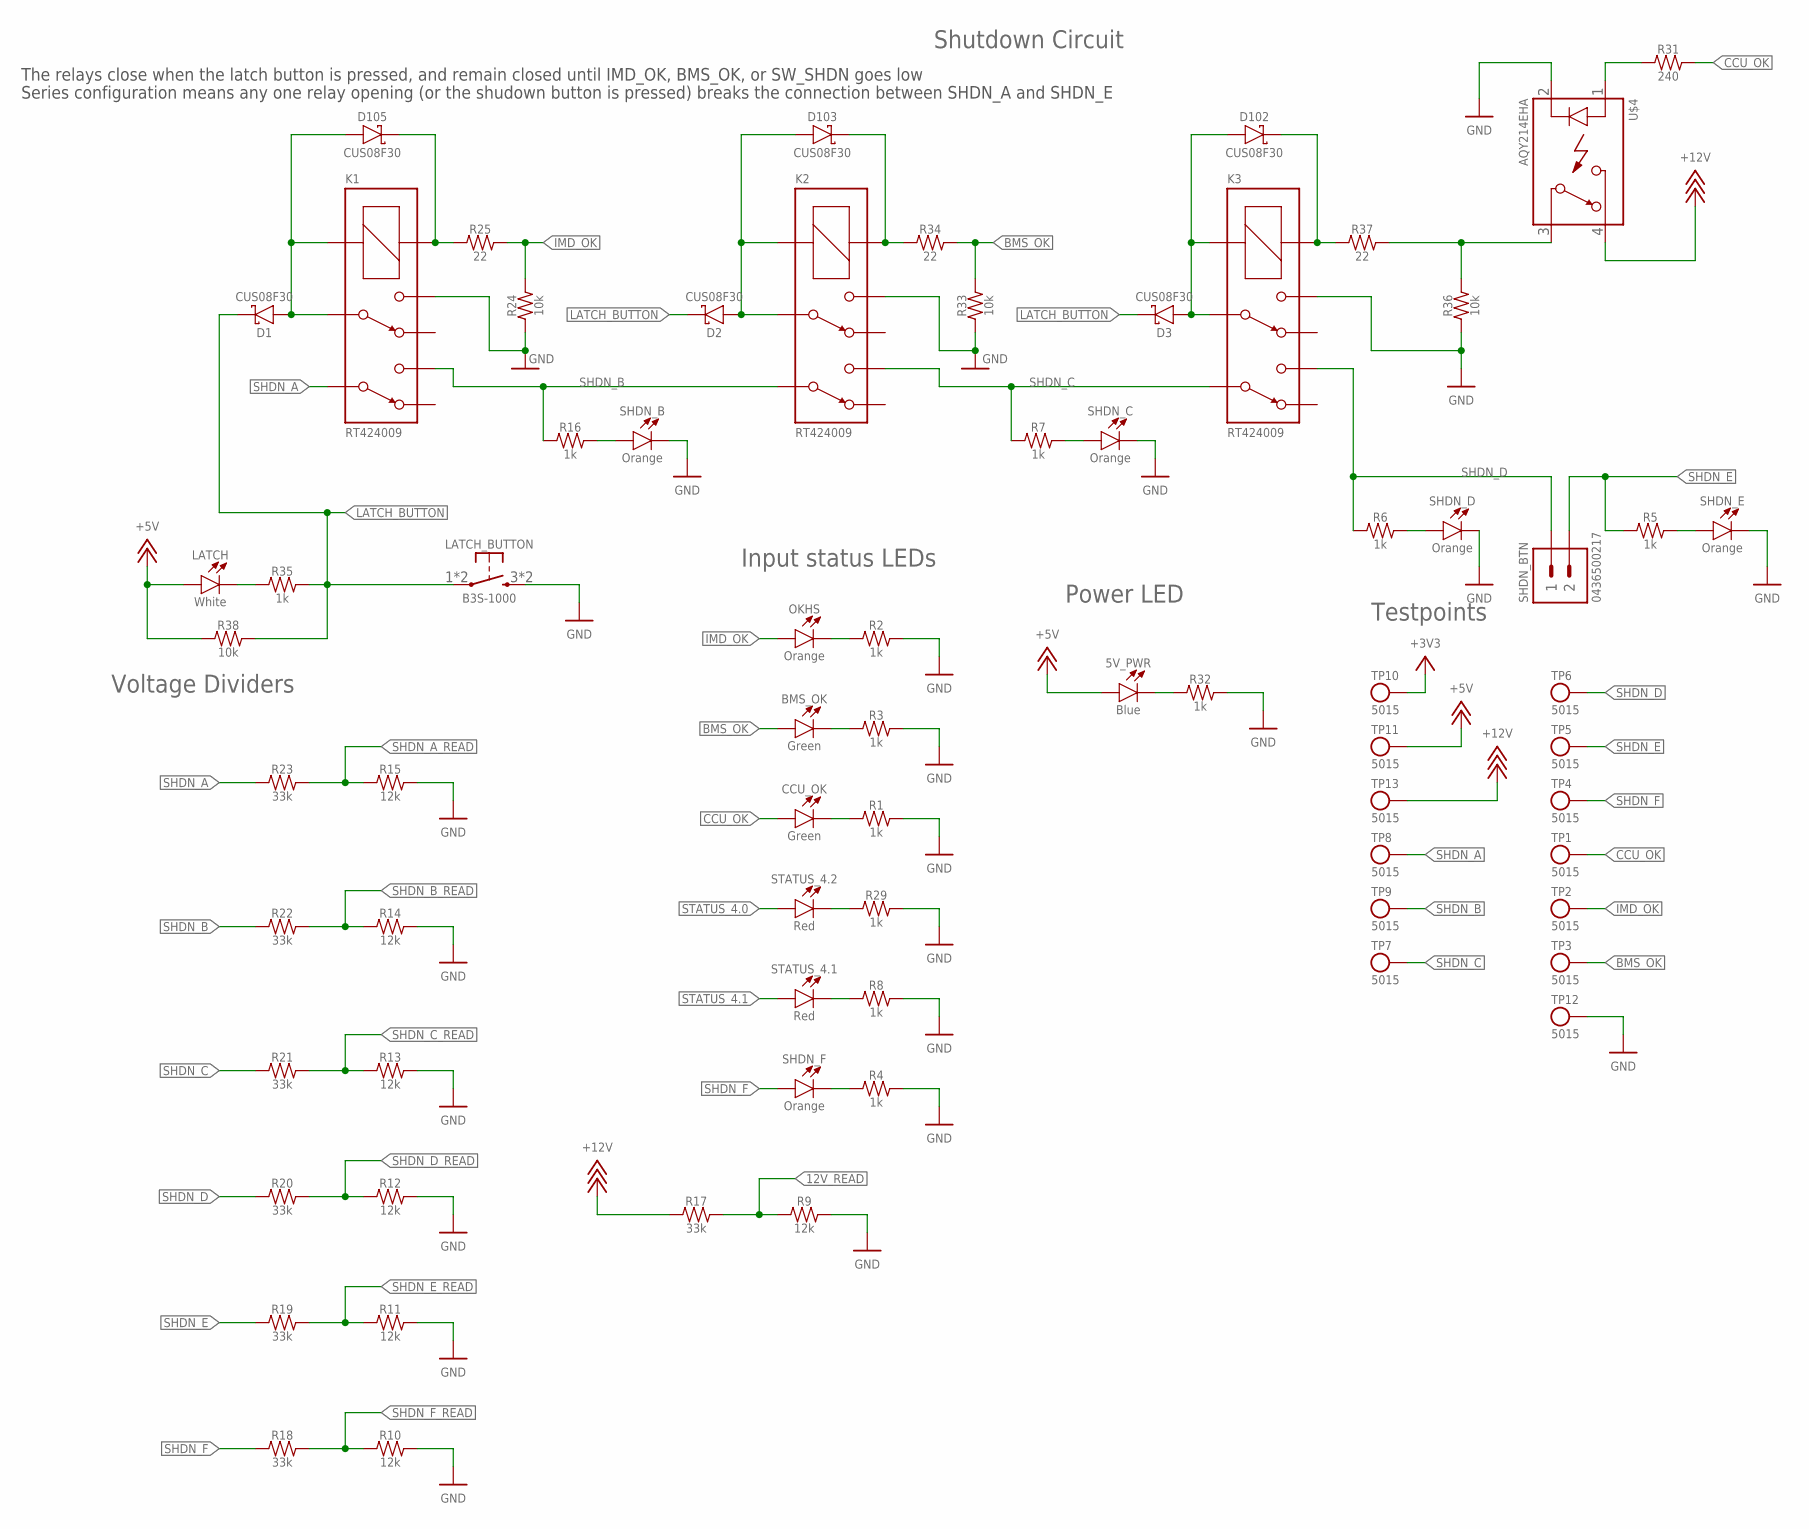
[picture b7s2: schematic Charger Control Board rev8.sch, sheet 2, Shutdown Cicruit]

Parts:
5V_PWR: LED_0603_BLUE; 0603-LED
BMS_OK: LED_0603_GREEN; 0603-LED
CCU_OK: LED_0603_GREEN; 0603-LED
D1, D2, D3, D102, D103, D105: SCHOTTKY_SOD323_30V; SOD-323
K1, K2, K3: RELAY_DPDT; RT*2*
LATCH: LED_0603_WHITE; 0603-LED
LATCH_BUTTON: BUTTON; B3S-100X
OKHS: LED_0603_ORANGE; 0603-LED
R1, R2, R3, R4, R5, R6, R7, R8, R16, R29, R32, R35: RESISTOR_0603_1K; 0603-RES
R9, R10, R11, R12, R13, R14, R15: RESISTOR_0603_12K; 0603-RES
R17, R18, R19, R20, R21, R22, R23: RESISTOR_0603_33K; 0603-RES
R24, R33, R36, R38: RESISTOR_0603_10K; 0603-RES
R25, R34, R37: RESISTOR_0603_22; 0603-RES
R31: RESISTOR_0603_240; 0603-RES
SHDN_B: LED_0603_ORANGE; 0603-LED
SHDN_BTN: CONNECTOR-2_MF_T_V_; MOLEX_MICROFIT_PTH_VERTICAL_02_SINGLE
SHDN_C: LED_0603_ORANGE; 0603-LED
SHDN_D: LED_0603_ORANGE; 0603-LED
SHDN_E: LED_0603_ORANGE; 0603-LED
SHDN_F: LED_0603_ORANGE; 0603-LED
STATUS_4.1, STATUS_4.2: LED_0603_RED; 0603-LED
TP1, TP2, TP3, TP4, TP5, TP6, TP7, TP8, TP9, TP10, TP11, TP12, TP13: TEST_POINT; 5015
U$4: RELAY_SOLIDSTATE_NO; DIP-4

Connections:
12V_READ: R9.1, R17.2; also elsewhere on the board
+3V3: TP10.1; also elsewhere on the board
+5V: 5V_PWR.2 (A), LATCH.2 (A), R38.1, TP11.1; also elsewhere on the board
+12V: R17.1, TP13.1, U$4.4 (CONTACT2); also elsewhere on the board
BMS_OK: BMS_OK.2 (A), R33.2, R34.2, TP3.1; also elsewhere on the board
CCU_OK: CCU_OK.2 (A), R31.2, TP1.1; also elsewhere on the board
GND: K1.14 (4), K2.14 (4), K3.14 (4), LATCH_BUTTON.3 (S), LATCH_BUTTON.4 (S), R1.2, R2.2, R3.2, R4.2, R8.2, R9.2, R10.2, R11.2, R12.2, R13.2, R14.2, R15.2, R24.1, R29.2, R32.2, R33.1, R36.1, SHDN_B.1 (C), SHDN_C.1 (C), SHDN_D.1 (C), SHDN_E.1 (C), TP12.1, U$4.2 (CONTROL-); also elsewhere on the board
IMD_OK: OKHS.2 (A), R24.2, R25.2, TP2.1; also elsewhere on the board
LATCH_BUTTON: D1.C, D2.C, D3.C, LATCH_BUTTON.1, LATCH_BUTTON.2, R35.2, R38.2
unnamed: R4.1, SHDN_F.1 (C)
unnamed: R31.1, U$4.1 (CONTROL+)
unnamed: D1.A, D105.A, K1.11 (3), K1.A2 (COIL-)
unnamed: D105.C, K1.A1 (COIL+), R25.1
unnamed: D103.C, K2.A1 (COIL+), R34.1
unnamed: D2.A, D103.A, K2.11 (3), K2.A2 (COIL-)
unnamed: D102.C, K3.A1 (COIL+), R37.1
unnamed: R36.2, R37.2, U$4.3 (CONTACT1)
unnamed: LATCH.1 (C), R35.1
unnamed: R6.2, SHDN_D.2 (A)
unnamed: R5.2, SHDN_E.2 (A)
unnamed: D3.A, D102.A, K3.11 (3), K3.A2 (COIL-)
unnamed: R7.2, SHDN_C.2 (A)
unnamed: R16.2, SHDN_B.2 (A)
unnamed: OKHS.1 (C), R2.1
unnamed: BMS_OK.1 (C), R3.1
unnamed: CCU_OK.1 (C), R1.1
unnamed: R29.1, STATUS_4.2.1 (C)
unnamed: 5V_PWR.1 (C), R32.1
unnamed: R8.1, STATUS_4.1.1 (C)
SHDN_A: K1.21 (6), R23.1, TP8.1; also elsewhere on the board
SHDN_A_READ: R15.1, R23.2; also elsewhere on the board
SHDN_B: K1.24 (5), K2.21 (6), R16.1, R22.1, TP9.1
SHDN_B_READ: R14.1, R22.2; also elsewhere on the board
SHDN_C: K2.24 (5), K3.21 (6), R7.1, R21.1, TP7.1
SHDN_C_READ: R13.1, R21.2; also elsewhere on the board
SHDN_D: K3.24 (5), R6.1, R20.1, SHDN_BTN.1, TP6.1
SHDN_D_READ: R12.1, R20.2; also elsewhere on the board
SHDN_E: R5.1, R19.1, SHDN_BTN.2, TP5.1; also elsewhere on the board
SHDN_E_READ: R11.1, R19.2; also elsewhere on the board
SHDN_F: R18.1, SHDN_F.2 (A), TP4.1; also elsewhere on the board
SHDN_F_READ: R10.1, R18.2; also elsewhere on the board
STATUS_4.0: STATUS_4.2.2 (A); also elsewhere on the board
STATUS_4.1: STATUS_4.1.2 (A); also elsewhere on the board

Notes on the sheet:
Input status LEDs
Power LED
Voltage Dividers
Shutdown Circuit
Testpoints
The relays close when the latch button is pressed, and remain closed until IMD_OK, BMS_OK, or SW_SHDN goes low
Series configuration means any one relay opening (or the shudown button is pressed) breaks the connection between SHDN_A and SHDN_E
